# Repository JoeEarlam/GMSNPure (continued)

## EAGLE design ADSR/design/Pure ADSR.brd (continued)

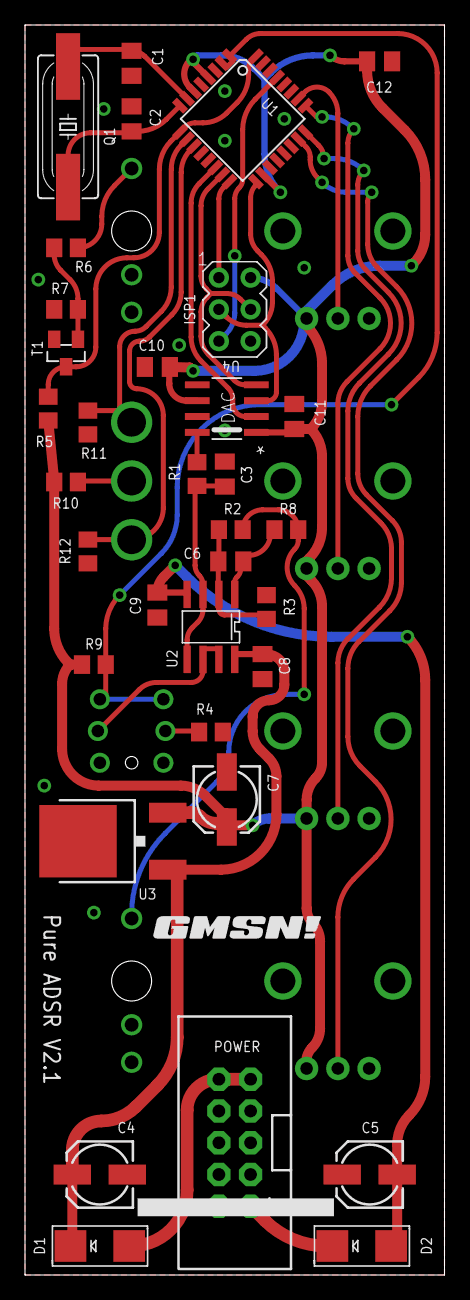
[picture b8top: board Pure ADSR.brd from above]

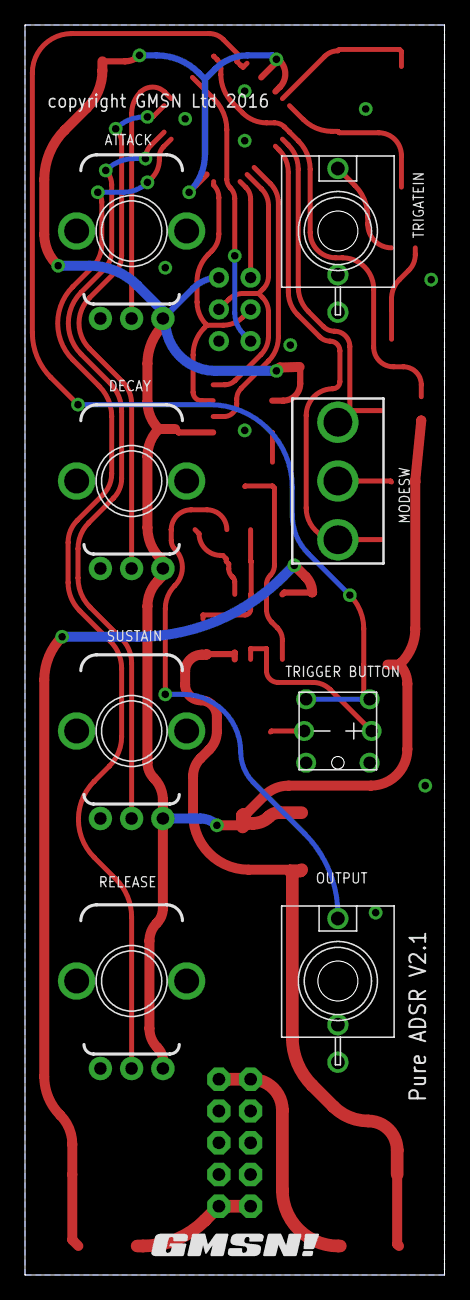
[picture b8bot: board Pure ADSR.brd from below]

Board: 2 copper layers, 33.6 x 100.0 mm, 44 parts (9 on the bottom side), 31 nets.

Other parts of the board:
U3: 7805; V-REG
U$1, U$2: GMSN!_LOGO

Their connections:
+5V: U3.3; also elsewhere on the board
+12V: U3.1; also elsewhere on the board
GND: U3.4; also elsewhere on the board

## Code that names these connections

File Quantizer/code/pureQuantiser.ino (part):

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#include <EEPROM.h>

//Setup LED Pin Varibles
const byte LR_0 = A3;
const byte LR_1 = A4;
const byte LR_2 = A5;
const byte LR_3 = 7;
const byte LC_0 = A0;
const byte LC_1 = A1;
const byte LC_2 = A2;

//Setup Button Pin Variable
const byte BC_0 = 2;
const byte BC_1 = 1;
const byte BC_2 = 0;
const byte BR_0 = 3;
const byte BR_1 = 4;
const byte BR_2 = 5;
const byte BR_3 = 6;

//Setup variable for the buttons, LEDs and temperament
int note;
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int lastCvOut;
unsigned long lastCvChange;
int triggerOnTime = 10;
const byte trig = 8;

void setup() {

  //Setup LED Pins
  pinMode(LR_0, OUTPUT);
  pinMode(LR_1, OUTPUT);
  pinMode(LR_2, OUTPUT);
  pinMode(LR_3, OUTPUT);
  pinMode(LC_0, OUTPUT);
  pinMode(LC_1, OUTPUT);
  pinMode(LC_2, OUTPUT);

  digitalWrite(LR_0, HIGH);
  digitalWrite(LR_1, HIGH);
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  digitalWrite(LC_2, LOW);

  //Setup Button Pins
  pinMode(BC_0, OUTPUT);
  pinMode(BC_1, OUTPUT);
  pinMode(BC_2, OUTPUT);
  pinMode(BR_0, INPUT);
  pinMode(BR_1, INPUT);
  pinMode(BR_2, INPUT);
  pinMode(BR_3, INPUT);

  digitalWrite(BC_0, LOW);
  digitalWrite(BC_1, LOW);
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  SPI.begin();

  //Setup Trigger Pin
  pinMode(trig, OUTPUT);
  digitalWrite(trig, LOW);

  //Read last saved notes from EEPROM
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
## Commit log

2019-05-15 re-organised slightly more sensibly
2019-05-15 added through hole clouds
2019-05-15 added more modules
2019-05-27 added code for ADSR, Quantiser and Sequencer
